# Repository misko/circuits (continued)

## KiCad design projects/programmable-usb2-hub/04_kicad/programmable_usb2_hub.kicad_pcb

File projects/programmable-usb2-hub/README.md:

# Programmable USB 2.0 hub

Four-port, self-powered USB 2.0 hub with 5 V / 3 A available at each
downstream USB-A receptacle. A USB-connected management controller provides
per-port power switching, physical D+/D- connection control, fault and power
telemetry, and a host utility that combines commanded state with the hub's
actual attach/enumeration state.

Status: commission complete; architecture and sourcing spike in progress.

Current release: none.

Build entry point: `bash 03_src/rebuild_all.sh` after the schematic and rules
stages are complete.

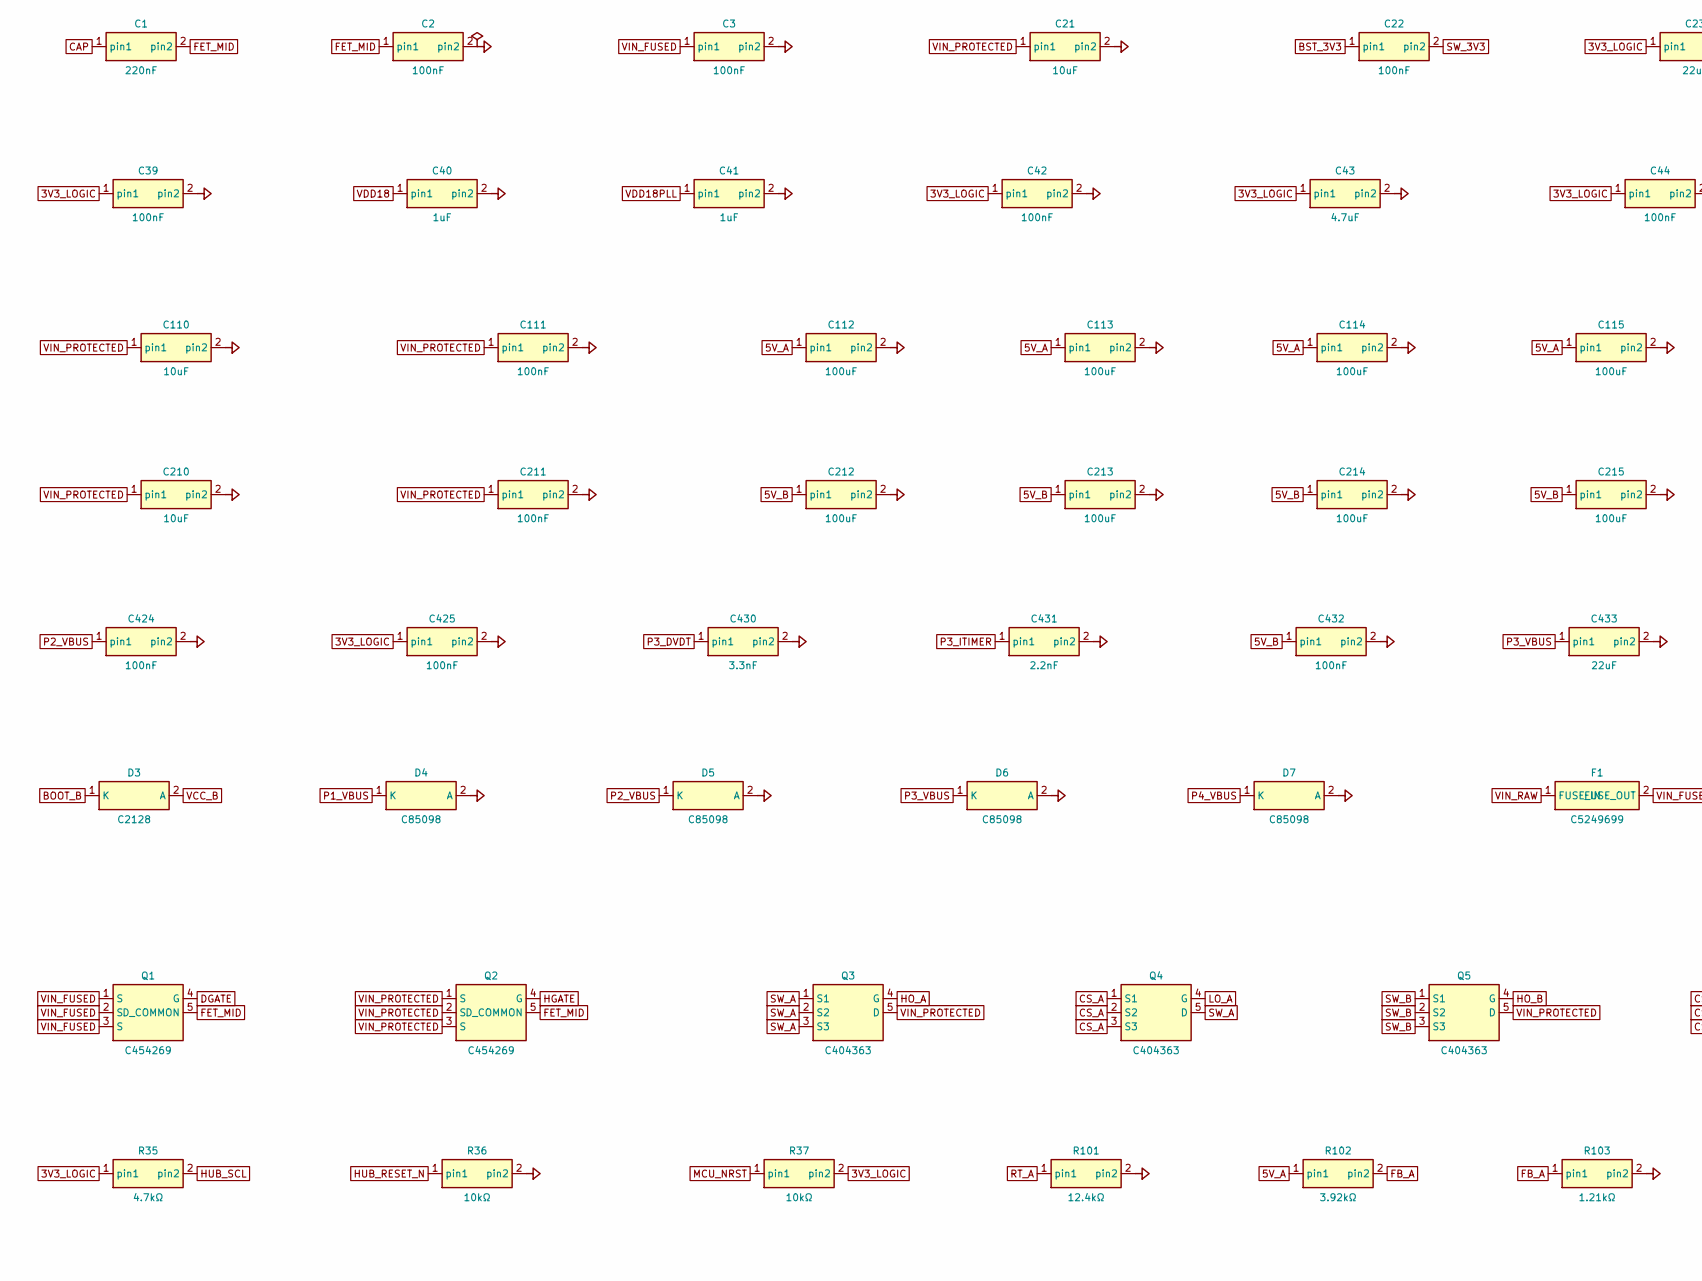
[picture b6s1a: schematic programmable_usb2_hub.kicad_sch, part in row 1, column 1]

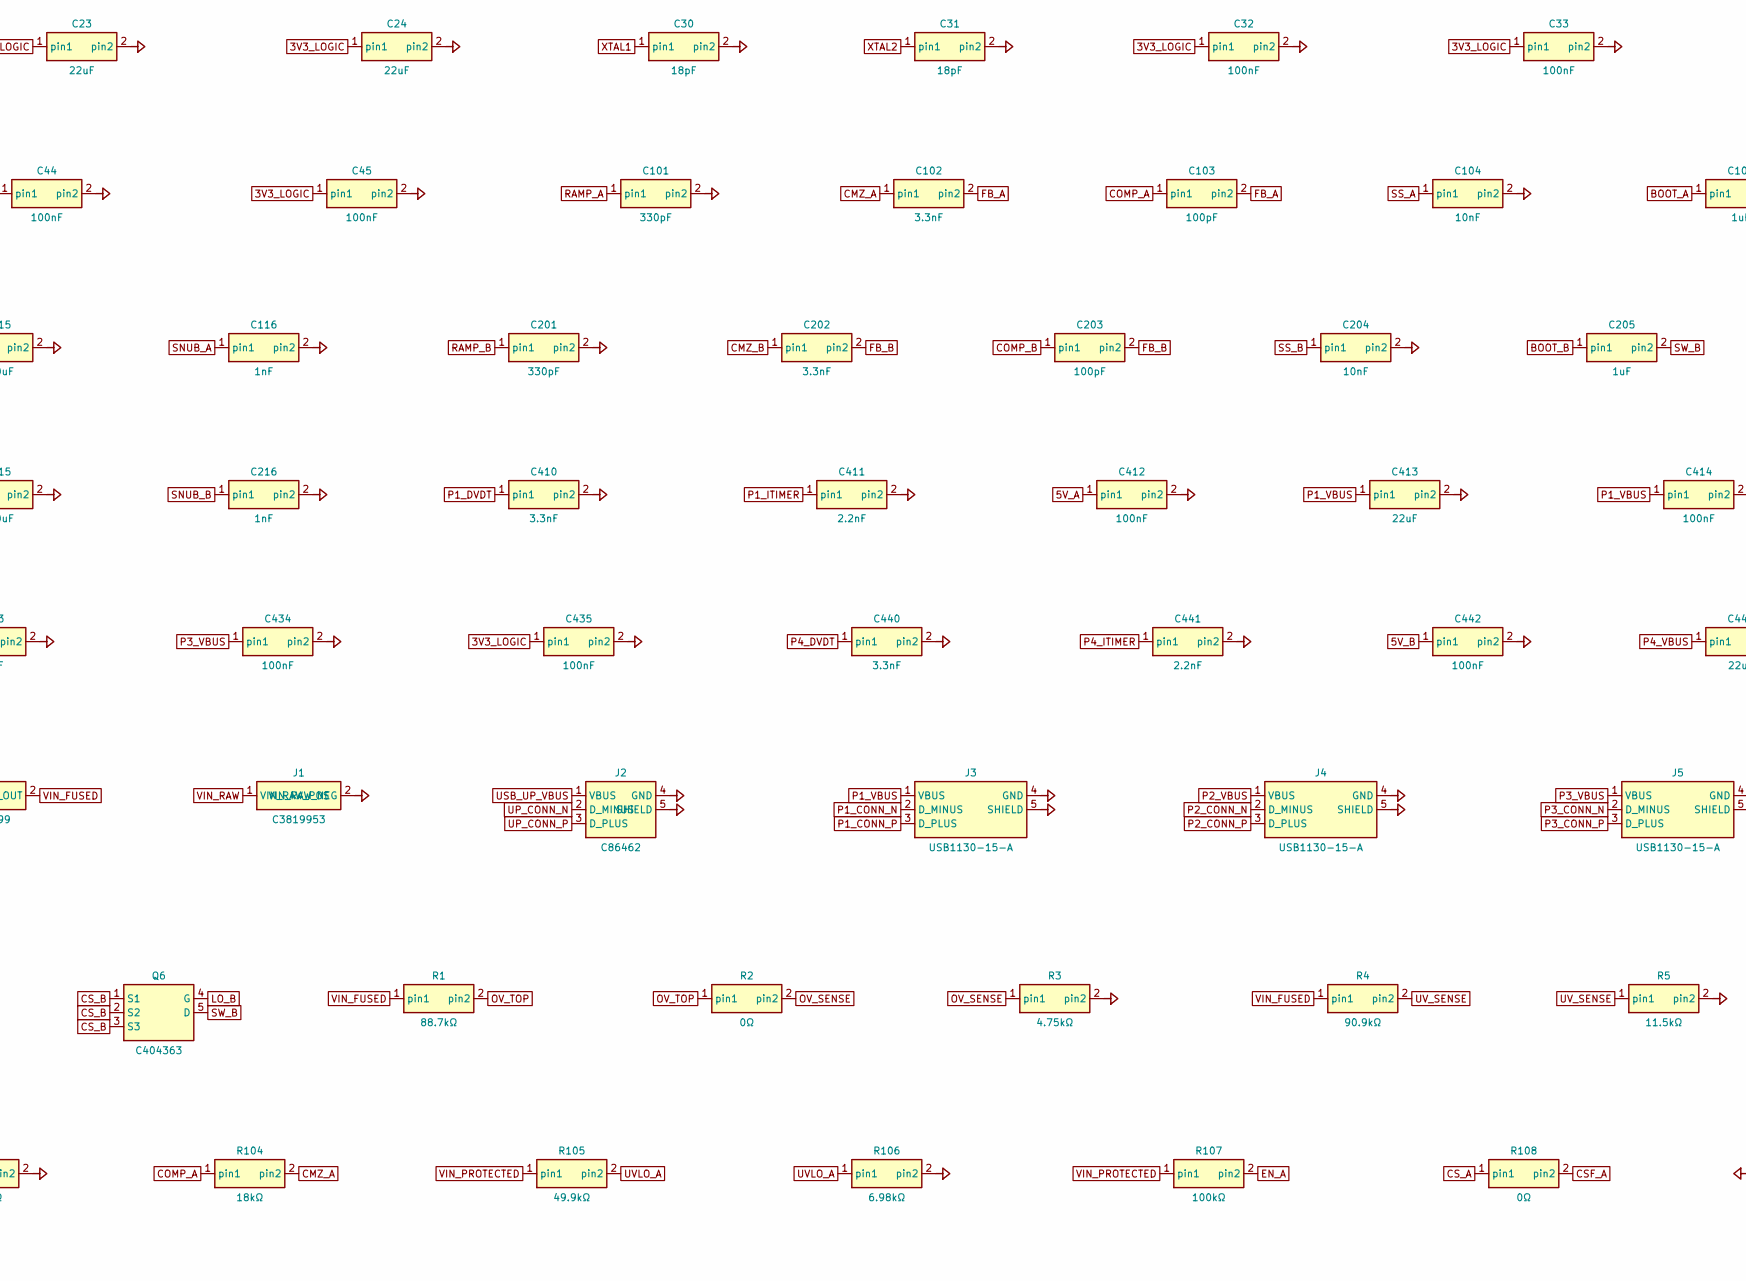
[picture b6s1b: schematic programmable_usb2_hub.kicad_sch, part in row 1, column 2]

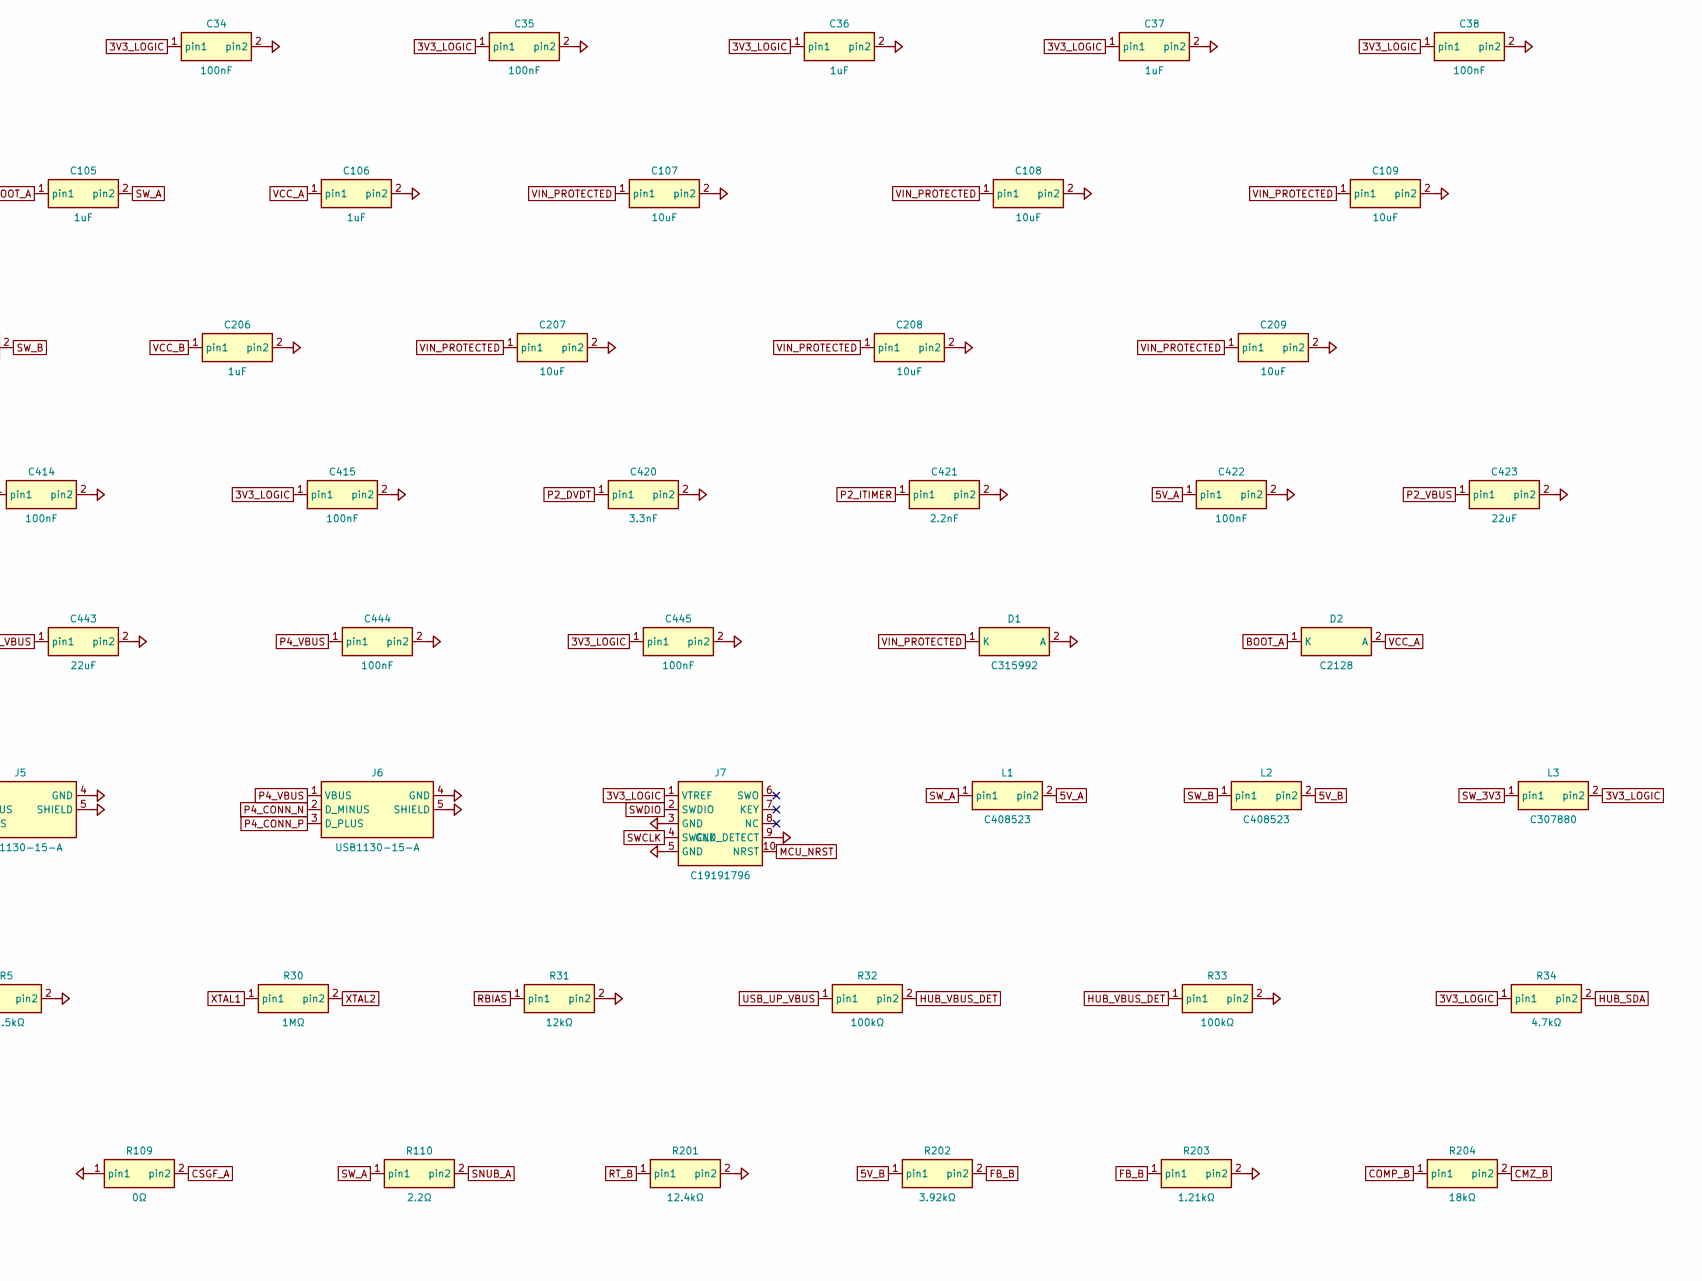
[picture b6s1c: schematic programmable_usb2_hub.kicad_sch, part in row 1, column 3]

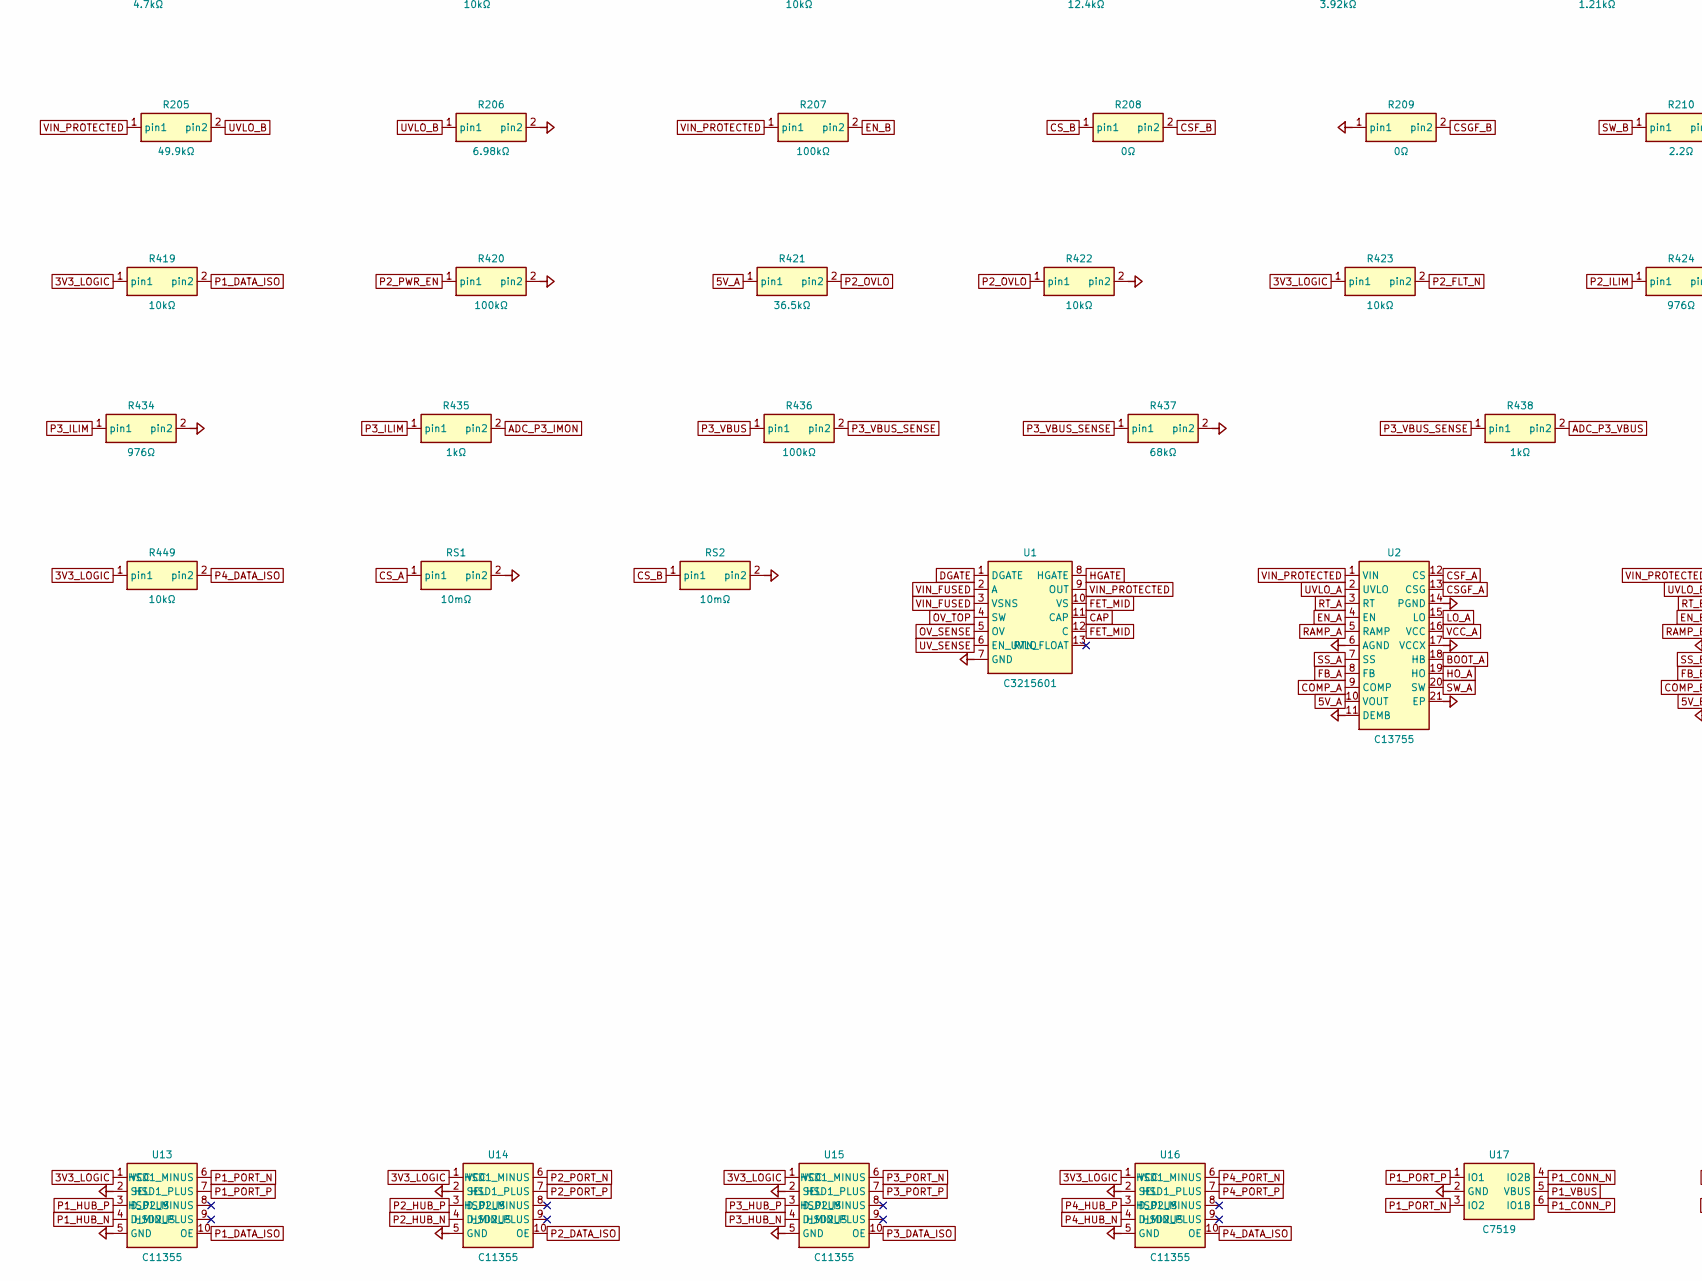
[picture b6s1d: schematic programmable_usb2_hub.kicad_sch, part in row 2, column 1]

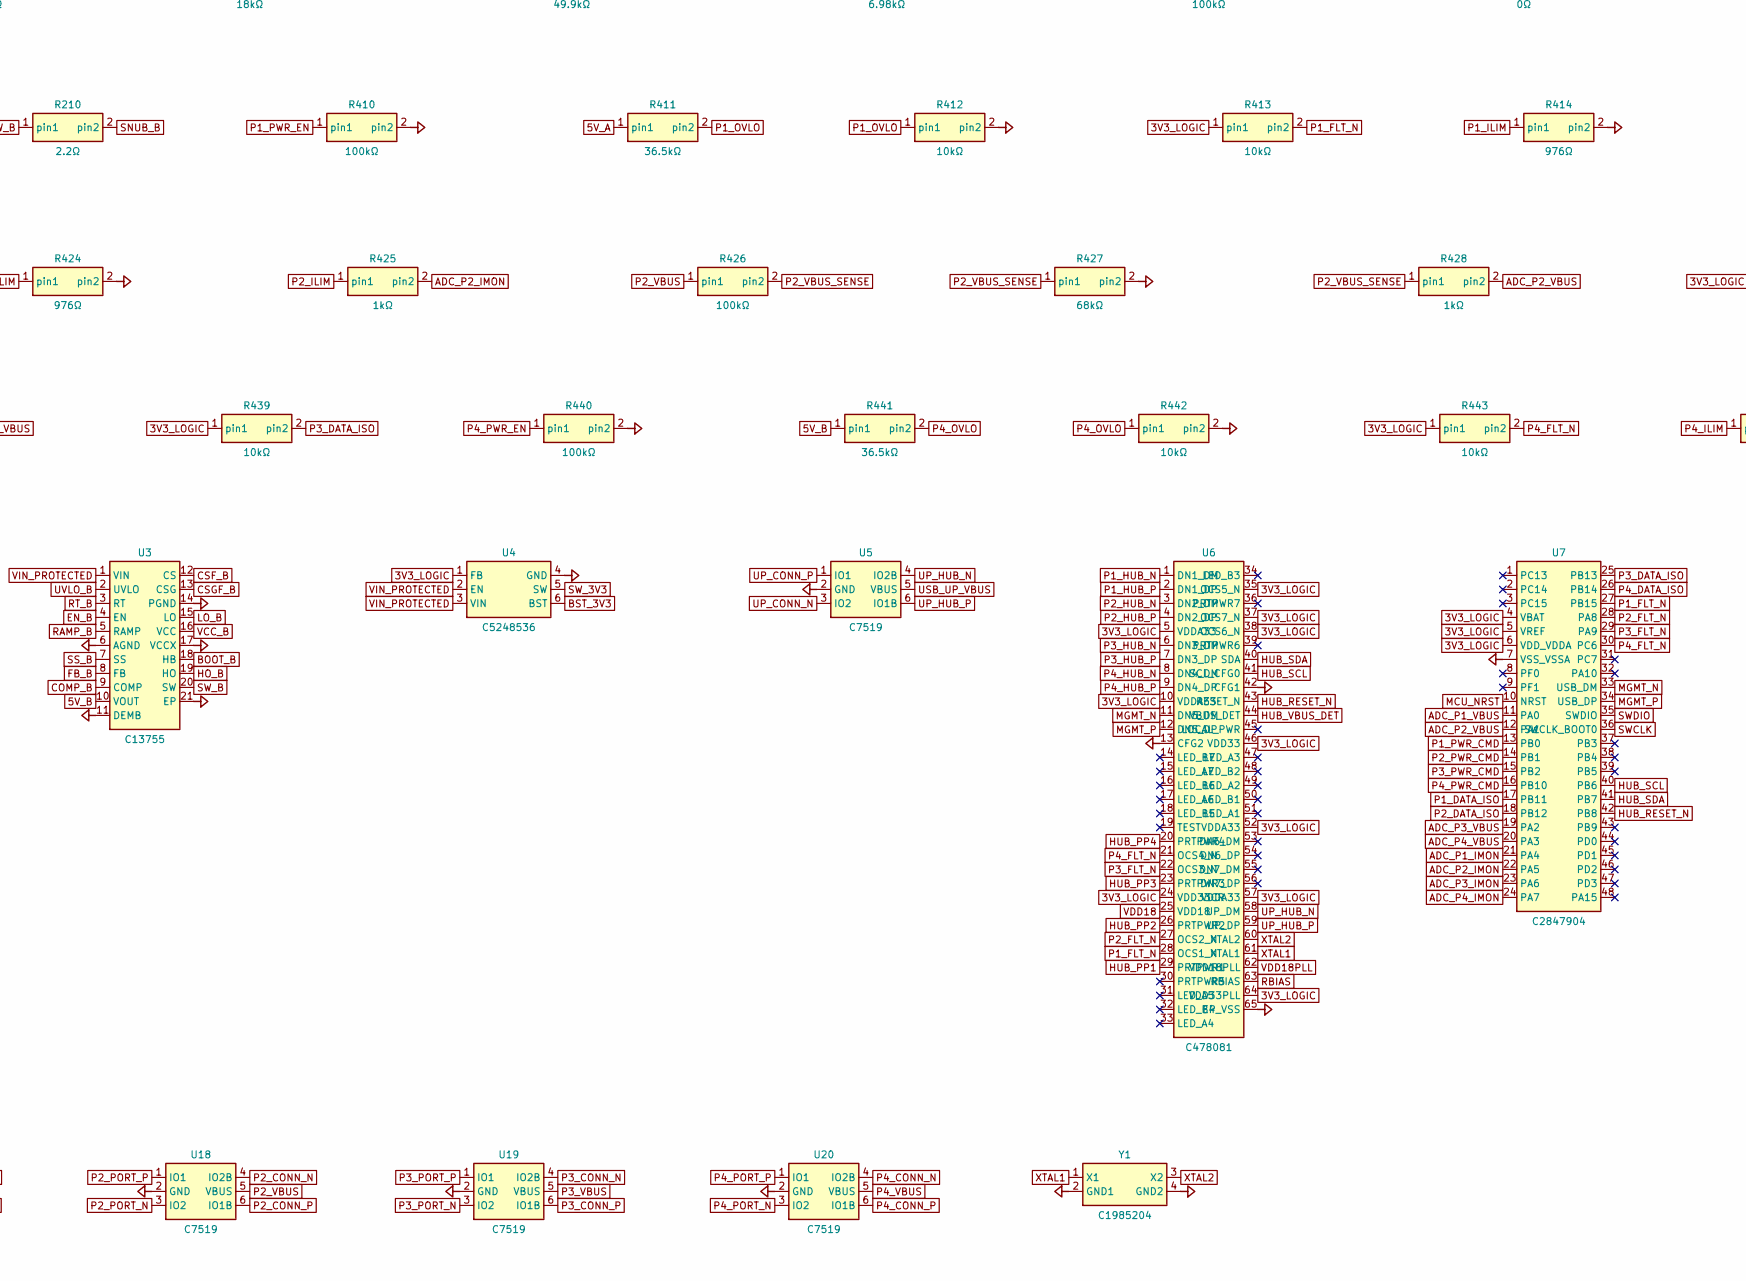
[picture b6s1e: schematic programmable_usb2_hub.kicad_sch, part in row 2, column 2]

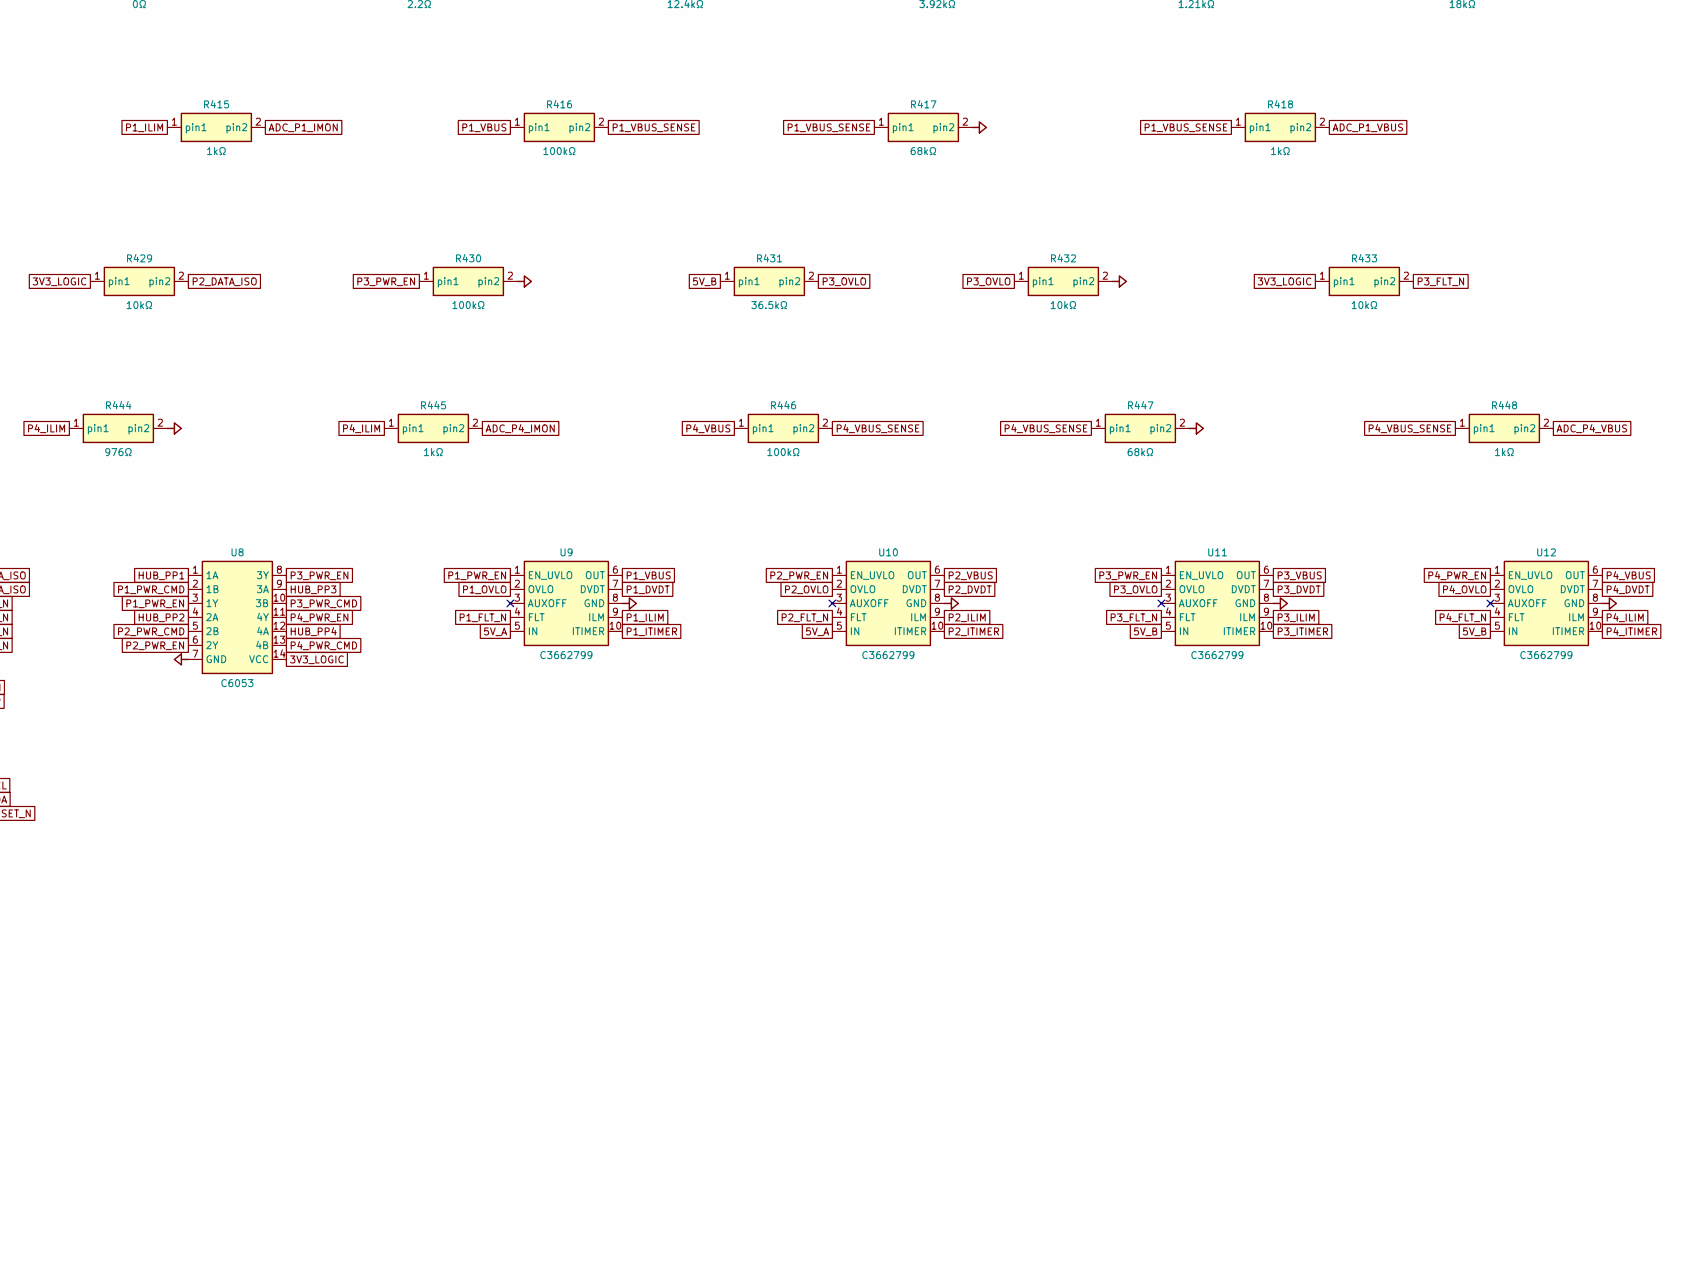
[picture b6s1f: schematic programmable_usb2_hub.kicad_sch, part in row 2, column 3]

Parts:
C1: 220nF; C_0603_1608Metric
C2, C3: 100nF; C_1206_3216Metric
C21: 10uF; C_1206_3216Metric
C22, C32, C33, C34, C35, C38, C39, C42, C44, C45, C111, C211, C412, C414, C415, C422, C424, C425, C432, C434, C435, C442, C444, C445: 100nF; C_0603_1608Metric
C23, C24: 22uF; C_1206_3216Metric
C30, C31: 18pF; C_0603_1608Metric
C36, C37, C40, C41, C105, C106, C205, C206: 1uF; C_0603_1608Metric
C43: 4.7uF; C_0603_1608Metric
C101, C201: 330pF; C_0603_1608Metric
C102, C202, C410, C420, C430, C440: 3.3nF; C_0603_1608Metric
C103, C203: 100pF; C_0603_1608Metric
C104, C204: 10nF; C_0603_1608Metric
C107, C108, C109, C110, C207, C208, C209, C210: 10uF; C_1210_3225Metric
C112, C113, C114, C115, C212, C213, C214, C215: 100uF; C_1210_3225Metric
C116, C216: 1nF; C_0805_2012Metric
C411, C421, C431, C441: 2.2nF; C_0603_1608Metric
C413, C423, C433, C443: 22uF; C_1210_3225Metric
D1: C315992; D_SMB
D2, D3: C2128; D_SOD-323
D4, D5, D6, D7: C85098; D_SMA
F1: C5249699; Fuseholder_Blade_Mini_Keystone_3568
J1: C3819953; TerminalBlock_KANGNEX_WJ126V_2P_P5.0
J2: C86462; USB_B_TE_292304-1_Horizontal
J3, J4, J5, J6: USB1130-15-A; USB_A_GCT_USB1130_Horizontal
J7: C19191796; PinHeader_2x05_P1.27mm_Vertical
L1, L2: C408523; L_Sunlord_MWSA1206S-6R8
L3: C307880; L_TDK_VLS6045EX_VLS6045AF
Q1, Q2: C454269; TDSON-8-1
Q3, Q4, Q5, Q6: C404363; PowerPAK_SO-8_Single_Paste65
R1: 88.7kΩ; R_0603_1608Metric
R2, R108, R109, R208, R209: 0Ω; R_0603_1608Metric
R3: 4.75kΩ; R_0603_1608Metric
R4: 90.9kΩ; R_0603_1608Metric
R5: 11.5kΩ; R_0603_1608Metric
R30: 1MΩ; R_0603_1608Metric
R31: 12kΩ; R_0603_1608Metric
R32, R33, R107, R207, R410, R416, R420, R426, R430, R436, R440, R446: 100kΩ; R_0603_1608Metric
R34, R35: 4.7kΩ; R_0603_1608Metric
R36, R37, R412, R413, R419, R422, R423, R429, R432, R433, R439, R442, R443, R449: 10kΩ; R_0603_1608Metric
R101, R201: 12.4kΩ; R_0603_1608Metric
R102, R202: 3.92kΩ; R_0603_1608Metric
R103, R203: 1.21kΩ; R_0603_1608Metric
R104, R204: 18kΩ; R_0603_1608Metric
R105, R205: 49.9kΩ; R_0603_1608Metric
R106, R206: 6.98kΩ; R_0603_1608Metric
R110, R210: 2.2Ω; R_1206_3216Metric
R411, R421, R431, R441: 36.5kΩ; R_0603_1608Metric
R414, R424, R434, R444: 976Ω; R_0603_1608Metric
R415, R418, R425, R428, R435, R438, R445, R448: 1kΩ; R_0603_1608Metric
R417, R427, R437, R447: 68kΩ; R_0603_1608Metric
RS1, RS2: 10mΩ; R_2512_6332Metric
U1: C3215601; WSON-12-1EP_3x3mm_P0.5mm_EP1.5x2.5mm
U2, U3: C13755; HTSSOP-20-1EP_4.4x6.5mm_P0.65mm_EP3.4x6.5mm_Mask2.75x3.43mm
U4: C5248536; TSOT-23-6
U5, U17, U18, U19, U20: C7519; SOT-23-6
U6: C478081; QFN-64-1EP_9x9mm_P0.5mm_EP4.7x4.7mm_ThermalVias
U7: C2847904; LQFP-48_7x7mm_P0.5mm
U8: C6053; TSSOP-14_4.4x5mm_P0.65mm
U9, U10, U11, U12: C3662799; Texas_RPW0010A_VQFN-HR-10_2x2mm_P0.45mm_ThermalVias
U13, U14, U15, U16: C11355; MSOP-10_3x3mm_P0.5mm
Y1: C1985204; Crystal_SMD_3225-4Pin_3.2x2.5mm

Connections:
3V3_LOGIC: C23.1, C24.1, C32.1, C33.1, C34.1, C35.1, C36.1, C37.1, C38.1, C39.1, C42.1, C43.1, C44.1, C45.1, C415.1, C425.1, C435.1, C445.1, J7.1 (VTREF), L3.2, R34.1, R35.1, R37.2, R413.1, R419.1, R423.1, R429.1, R433.1, R439.1, R443.1, R449.1, U4.1 (FB), U6.5 (VDDA33), U6.10 (VDDA33), U6.24 (VDD33CR), U6.35 (OCS5_N), U6.37 (OCS7_N), U6.38 (OCS6_N), U6.46 (VDD33), U6.52 (VDDA33), U6.57 (VDDA33), U6.64 (VDD33PLL), U7.4 (VBAT), U7.5 (VREF), U7.6 (VDD_VDDA), U8.14 (VCC), U13.1 (VCC), U14.1 (VCC), U15.1 (VCC), U16.1 (VCC)
5V_A: C112.1, C113.1, C114.1, C115.1, C412.1, C422.1, L1.2, R102.1, R411.1, R421.1, U2.10 (VOUT), U9.5 (IN), U10.5 (IN)
5V_B: C212.1, C213.1, C214.1, C215.1, C432.1, C442.1, L2.2, R202.1, R431.1, R441.1, U3.10 (VOUT), U11.5 (IN), U12.5 (IN)
ADC_P1_IMON: R415.2, U7.21 (PA4)
ADC_P1_VBUS: R418.2, U7.11 (PA0)
ADC_P2_IMON: R425.2, U7.22 (PA5)
ADC_P2_VBUS: R428.2, U7.12 (PA1)
ADC_P3_IMON: R435.2, U7.23 (PA6)
ADC_P3_VBUS: R438.2, U7.19 (PA2)
ADC_P4_IMON: R445.2, U7.24 (PA7)
ADC_P4_VBUS: R448.2, U7.20 (PA3)
BOOT_A: C105.1, D2.1 (K), U2.18 (HB)
BOOT_B: C205.1, D3.1 (K), U3.18 (HB)
BST_3V3: C22.1, U4.6 (BST)
CAP: C1.1, U1.11 (CAP)
CMZ_A: C102.1, R104.2
CMZ_B: C202.1, R204.2
COMP_A: C103.1, R104.1, U2.9 (COMP)
COMP_B: C203.1, R204.1, U3.9 (COMP)
CSF_A: R108.2, U2.12 (CS)
CSF_B: R208.2, U3.12 (CS)
CSGF_A: R109.2, U2.13 (CSG)
CSGF_B: R209.2, U3.13 (CSG)
CS_A: Q4.1 (S1), Q4.2 (S2), Q4.3 (S3), R108.1, RS1.1
CS_B: Q6.1 (S1), Q6.2 (S2), Q6.3 (S3), R208.1, RS2.1
DGATE: Q1.4 (G), U1.1 (DGATE)
EN_A: R107.2, U2.4 (EN)
EN_B: R207.2, U3.4 (EN)
FB_A: C102.2, C103.2, R102.2, R103.1, U2.8 (FB)
FB_B: C202.2, C203.2, R202.2, R203.1, U3.8 (FB)
FET_MID: C1.2, C2.1, Q1.5 (D_COMMON), Q2.5 (D_COMMON), U1.10 (VS), U1.12 (C)
GND: C2.2, C3.2, C21.2, C23.2, C24.2, C30.2, C31.2, C32.2, C33.2, C34.2, C35.2, C36.2, C37.2, C38.2, C39.2, C40.2, C41.2, C42.2, C43.2, C44.2, C45.2, C101.2, C104.2, C106.2, C107.2, C108.2, C109.2, C110.2, C111.2, C112.2, C113.2, C114.2, C115.2, C116.2, C201.2, C204.2, C206.2, C207.2, C208.2, C209.2, C210.2, C211.2, C212.2, C213.2, C214.2, C215.2, C216.2, C410.2, C411.2, C412.2, C413.2, C414.2, C415.2, C420.2, C421.2, C422.2, C423.2, C424.2, C425.2, C430.2, C431.2, C432.2, C433.2, C434.2, C435.2, C440.2, C441.2, C442.2, C443.2, C444.2, C445.2, D1.2 (A), D4.2 (A), D5.2 (A), D6.2 (A), D7.2 (A), J1.2 (VIN_RAW_NEG), J2.4 (GND), J2.5 (SHIELD), J3.4 (GND), J3.5 (SHIELD), J4.4 (GND), J4.5 (SHIELD), J5.4 (GND), J5.5 (SHIELD), J6.4 (GND), J6.5 (SHIELD), J7.3 (GND), J7.5 (GND), J7.9 (GND_DETECT), R3.2, R5.2, R31.2, R33.2, R36.2, R101.2, R103.2, R106.2, R109.1, R201.2, R203.2, R206.2, R209.1, R410.2, R412.2, R414.2, R417.2, R420.2, R422.2, R424.2, R427.2, R430.2, R432.2, R434.2, R437.2, R440.2, R442.2, R444.2, R447.2, RS1.2, RS2.2, U1.7 (GND), U2.6 (AGND), U2.11 (DEMB), U2.14 (PGND), U2.17 (VCCX), U2.21 (EP), U3.6 (AGND), U3.11 (DEMB), U3.14 (PGND), U3.17 (VCCX), U3.21 (EP), U4.4 (GND), U5.2 (GND), U6.13 (CFG2), U6.42 (CFG1), U6.65 (EP_VSS), U7.7 (VSS_VSSA), U8.7 (GND), U9.8 (GND), U10.8 (GND), U11.8 (GND), U12.8 (GND), U13.2 (SEL), U13.5 (GND), U14.2 (SEL), U14.5 (GND), U15.2 (SEL), U15.5 (GND), U16.2 (SEL), U16.5 (GND), U17.2 (GND), U18.2 (GND), U19.2 (GND), U20.2 (GND), Y1.2 (GND1), Y1.4 (GND2)
HGATE: Q2.4 (G), U1.8 (HGATE)
HO_A: Q3.4 (G), U2.19 (HO)
HO_B: Q5.4 (G), U3.19 (HO)
HUB_PP1: U6.29 (PRTPWR1), U8.1 (1A)
HUB_PP2: U6.26 (PRTPWR2), U8.4 (2A)
HUB_PP3: U6.23 (PRTPWR3), U8.9 (3A)
HUB_PP4: U6.20 (PRTPWR4), U8.12 (4A)
HUB_RESET_N: R36.1, U6.43 (RESET_N), U7.42 (PB8)
HUB_SCL: R35.2, U6.41 (SCL_CFG0), U7.40 (PB6)
HUB_SDA: R34.2, U6.40 (SDA), U7.41 (PB7)
HUB_VBUS_DET: R32.2, R33.1, U6.44 (VBUS_DET)
LO_A: Q4.4 (G), U2.15 (LO)
LO_B: Q6.4 (G), U3.15 (LO)
MCU_NRST: J7.10 (NRST), R37.1, U7.10 (NRST)
MGMT_N: U6.11 (DN5_DM), U7.33 (USB_DM)
MGMT_P: U6.12 (DN5_DP), U7.34 (USB_DP)
OV_SENSE: R2.2, R3.1, U1.5 (OV)
OV_TOP: R1.2, R2.1, U1.4 (SW)
P1_CONN_N: J3.2 (D_MINUS), U17.4 (IO2B)
P1_CONN_P: J3.3 (D_PLUS), U17.6 (IO1B)
P1_DATA_ISO: R419.2, U7.17 (PB11), U13.10 (OE)
P1_DVDT: C410.1, U9.7 (DVDT)
P1_FLT_N: R413.2, U6.28 (OCS1_N), U7.27 (PB15), U9.4 (FLT)
P1_HUB_N: U6.1 (DN1_DM), U13.4 (D_MINUS)
P1_HUB_P: U6.2 (DN1_DP), U13.3 (D_PLUS)
P1_ILIM: R414.1, R415.1, U9.9 (ILM)
P1_ITIMER: C411.1, U9.10 (ITIMER)
P1_OVLO: R411.2, R412.1, U9.2 (OVLO)
P1_PORT_N: U13.6 (HSD1_MINUS), U17.3 (IO2)
P1_PORT_P: U13.7 (HSD1_PLUS), U17.1 (IO1)
P1_PWR_CMD: U7.13 (PB0), U8.2 (1B)
P1_PWR_EN: R410.1, U8.3 (1Y), U9.1 (EN_UVLO)
P1_VBUS: C413.1, C414.1, D4.1 (K), J3.1 (VBUS), R416.1, U9.6 (OUT), U17.5 (VBUS)
P1_VBUS_SENSE: R416.2, R417.1, R418.1
P2_CONN_N: J4.2 (D_MINUS), U18.4 (IO2B)
P2_CONN_P: J4.3 (D_PLUS), U18.6 (IO1B)
P2_DATA_ISO: R429.2, U7.18 (PB12), U14.10 (OE)
P2_DVDT: C420.1, U10.7 (DVDT)
P2_FLT_N: R423.2, U6.27 (OCS2_N), U7.28 (PA8), U10.4 (FLT)
P2_HUB_N: U6.3 (DN2_DM), U14.4 (D_MINUS)
P2_HUB_P: U6.4 (DN2_DP), U14.3 (D_PLUS)
P2_ILIM: R424.1, R425.1, U10.9 (ILM)
P2_ITIMER: C421.1, U10.10 (ITIMER)
P2_OVLO: R421.2, R422.1, U10.2 (OVLO)
P2_PORT_N: U14.6 (HSD1_MINUS), U18.3 (IO2)
P2_PORT_P: U14.7 (HSD1_PLUS), U18.1 (IO1)
P2_PWR_CMD: U7.14 (PB1), U8.5 (2B)
P2_PWR_EN: R420.1, U8.6 (2Y), U10.1 (EN_UVLO)
P2_VBUS: C423.1, C424.1, D5.1 (K), J4.1 (VBUS), R426.1, U10.6 (OUT), U18.5 (VBUS)
P2_VBUS_SENSE: R426.2, R427.1, R428.1
P3_CONN_N: J5.2 (D_MINUS), U19.4 (IO2B)
P3_CONN_P: J5.3 (D_PLUS), U19.6 (IO1B)
P3_DATA_ISO: R439.2, U7.25 (PB13), U15.10 (OE)
P3_DVDT: C430.1, U11.7 (DVDT)
P3_FLT_N: R433.2, U6.22 (OCS3_N), U7.29 (PA9), U11.4 (FLT)
P3_HUB_N: U6.6 (DN3_DM), U15.4 (D_MINUS)
P3_HUB_P: U6.7 (DN3_DP), U15.3 (D_PLUS)
P3_ILIM: R434.1, R435.1, U11.9 (ILM)
P3_ITIMER: C431.1, U11.10 (ITIMER)
P3_OVLO: R431.2, R432.1, U11.2 (OVLO)
P3_PORT_N: U15.6 (HSD1_MINUS), U19.3 (IO2)
P3_PORT_P: U15.7 (HSD1_PLUS), U19.1 (IO1)
P3_PWR_CMD: U7.15 (PB2), U8.10 (3B)
P3_PWR_EN: R430.1, U8.8 (3Y), U11.1 (EN_UVLO)
P3_VBUS: C433.1, C434.1, D6.1 (K), J5.1 (VBUS), R436.1, U11.6 (OUT), U19.5 (VBUS)
P3_VBUS_SENSE: R436.2, R437.1, R438.1
P4_CONN_N: J6.2 (D_MINUS), U20.4 (IO2B)
P4_CONN_P: J6.3 (D_PLUS), U20.6 (IO1B)
P4_DATA_ISO: R449.2, U7.26 (PB14), U16.10 (OE)
P4_DVDT: C440.1, U12.7 (DVDT)
P4_FLT_N: R443.2, U6.21 (OCS4_N), U7.30 (PC6), U12.4 (FLT)
P4_HUB_N: U6.8 (DN4_DM), U16.4 (D_MINUS)
P4_HUB_P: U6.9 (DN4_DP), U16.3 (D_PLUS)
P4_ILIM: R444.1, R445.1, U12.9 (ILM)
P4_ITIMER: C441.1, U12.10 (ITIMER)
P4_OVLO: R441.2, R442.1, U12.2 (OVLO)
P4_PORT_N: U16.6 (HSD1_MINUS), U20.3 (IO2)
P4_PORT_P: U16.7 (HSD1_PLUS), U20.1 (IO1)
P4_PWR_CMD: U7.16 (PB10), U8.13 (4B)
P4_PWR_EN: R440.1, U8.11 (4Y), U12.1 (EN_UVLO)
P4_VBUS: C443.1, C444.1, D7.1 (K), J6.1 (VBUS), R446.1, U12.6 (OUT), U20.5 (VBUS)
P4_VBUS_SENSE: R446.2, R447.1, R448.1
RAMP_A: C101.1, U2.5 (RAMP)
RAMP_B: C201.1, U3.5 (RAMP)
RBIAS: R31.1, U6.63 (RBIAS)
RT_A: R101.1, U2.3 (RT)
RT_B: R201.1, U3.3 (RT)
SNUB_A: C116.1, R110.2
SNUB_B: C216.1, R210.2
SS_A: C104.1, U2.7 (SS)
SS_B: C204.1, U3.7 (SS)
SWCLK: J7.4 (SWCLK), U7.36 (SWCLK_BOOT0)
SWDIO: J7.2 (SWDIO), U7.35 (SWDIO)
SW_3V3: C22.2, L3.1, U4.5 (SW)
SW_A: C105.2, L1.1, Q3.1 (S1), Q3.2 (S2), Q3.3 (S3), Q4.5 (D), R110.1, U2.20 (SW)
SW_B: C205.2, L2.1, Q5.1 (S1), Q5.2 (S2), Q5.3 (S3), Q6.5 (D), R210.1, U3.20 (SW)
UP_CONN_N: J2.2 (D_MINUS), U5.3 (IO2)
UP_CONN_P: J2.3 (D_PLUS), U5.1 (IO1)
UP_HUB_N: U5.4 (IO2B), U6.58 (UP_DM)
UP_HUB_P: U5.6 (IO1B), U6.59 (UP_DP)
USB_UP_VBUS: J2.1 (VBUS), R32.1, U5.5 (VBUS)
UVLO_A: R105.2, R106.1, U2.2 (UVLO)
UVLO_B: R205.2, R206.1, U3.2 (UVLO)
UV_SENSE: R4.2, R5.1, U1.6 (EN_UVLO)
VCC_A: C106.1, D2.2 (A), U2.16 (VCC)
VCC_B: C206.1, D3.2 (A), U3.16 (VCC)
VDD18: C40.1, U6.25 (VDD18)
VDD18PLL: C41.1, U6.62 (VDD18PLL)
VIN_FUSED: C3.1, F1.2 (FUSE_OUT), Q1.1 (S), Q1.2 (S), Q1.3 (S), R1.1, R4.1, U1.2 (A), U1.3 (VSNS)
VIN_PROTECTED: C21.1, C107.1, C108.1, C109.1, C110.1, C111.1, C207.1, C208.1, C209.1, C210.1, C211.1, D1.1 (K), Q2.1 (S), Q2.2 (S), Q2.3 (S), Q3.5 (D), Q5.5 (D), R105.1, R107.1, R205.1, R207.1, U1.9 (OUT), U2.1 (VIN), U3.1 (VIN), U4.2 (EN), U4.3 (VIN)
VIN_RAW: F1.1 (FUSE_IN), J1.1 (VIN_RAW_POS)
XTAL1: C30.1, R30.1, U6.61 (XTAL1), Y1.1 (X1)
XTAL2: C31.1, R30.2, U6.60 (XTAL2), Y1.3 (X2)

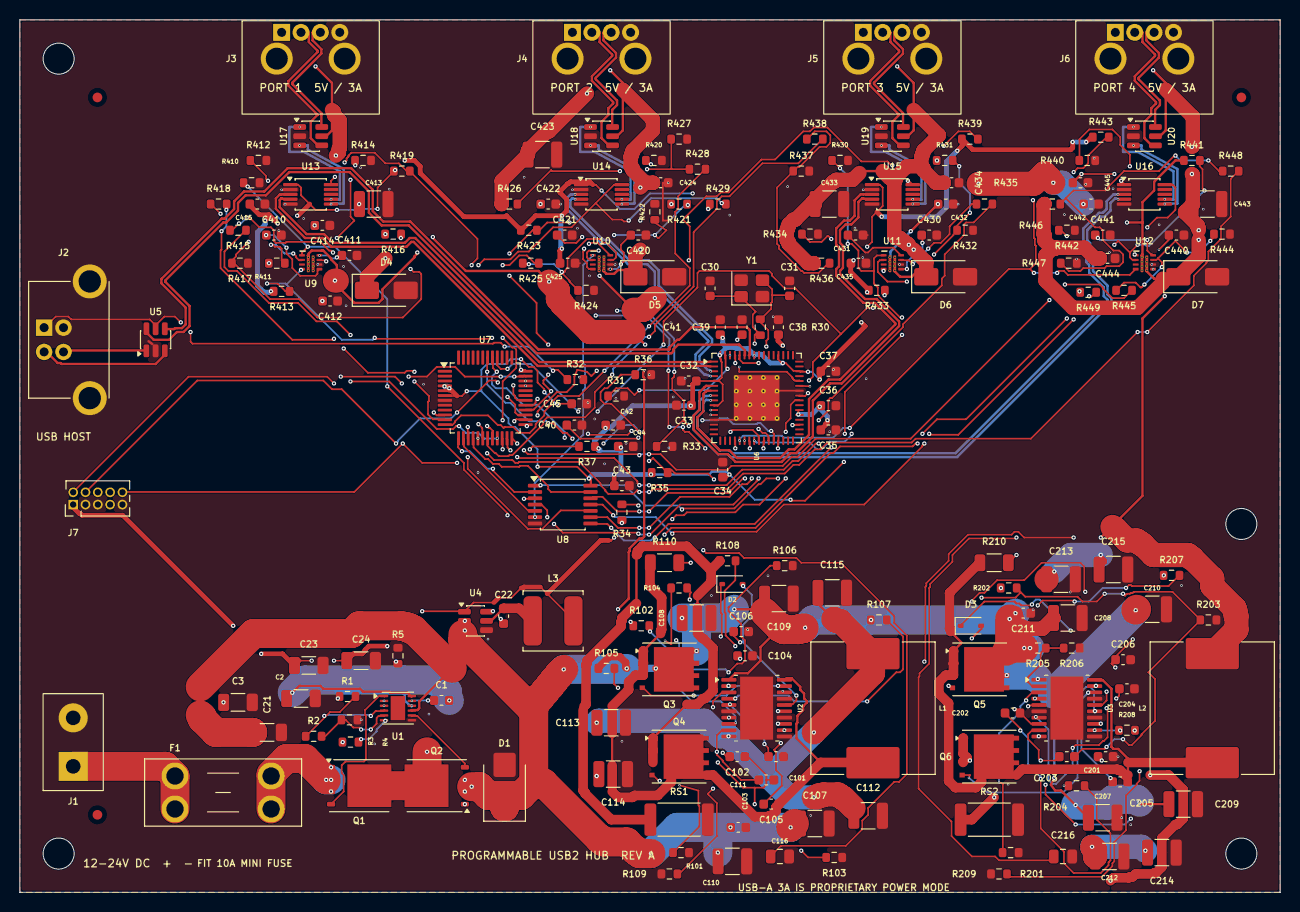
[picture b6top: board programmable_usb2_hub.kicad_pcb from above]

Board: 4 copper layers, 130.0 x 90.0 mm, 206 parts (0 on the bottom side), 145 nets.

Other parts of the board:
FID1, FID2, FID3: Fiducial_1mm_Mask2mm
H1, H2, H3, H4: MountingHole_3.2mm_M3
